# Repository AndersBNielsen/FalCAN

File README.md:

# FalCAN Probe

A compact USB 2.0 to CAN/RS‑485/RS‑422 hardware probe for interfacing and debugging CAN networks and differential serial buses. Designed in KiCad 9.
Firmware is here: <https://github.com/AndersBNielsen/FalCAN_fw>

## Can I buy one?
You can buy a FalCAN here: https://www.imania.dk/index.php?cPath=204&sort=5a&language=en

## Video overview
https://youtu.be/pHMQbOrLfP4

## Blog post
https://abnielsen.com/falcan

## Overview
- MCU: STM32F042C6Tx (USB FS device)
- CAN transceiver: SN65HVD230
- RS‑485/RS‑422 transceivers: SP3485EN (2x)
- USB‑C receptacle (HCTL HC‑TYPE‑C‑16P‑01A)
- 3.3V LDO regulator: MIC5504‑3.3
- Crystals: 8 MHz and 32.768 kHz
- CAN DE‑9 (female) connector for classic CAN pinout
- Jumpers/headers for boot, CAN, RS‑422/485 routing

Project metadata
- Title: FalCAN Probe
- Company: ABNielsen.com
- Revision: 0
- Board: 4‑layer FR4, ~1.6 mm 

## Repository Structure
- `USB-FalCAN.kicad_sch` — KiCad schematic
- `USB-FalCAN.kicad_pcb` — KiCad PCB layout
- `USB-FalCAN.kicad_pro` — KiCad project file
- `USB-FalCAN.kicad_prl` — KiCad project local settings
- `DSUB-9_... .kicad_mod` — Custom footprint for DE‑9 female connector
- `production/` — Fabrication outputs
  - `bom.csv` — Bill of Materials (includes LCSC part numbers)
  - `designators.csv` — Designator map
  - `positions.csv` — Pick‑and‑place (component positions)
  - `netlist.ipc` — IPC‑D‑356 netlist
  - `backups/` — Historical fabrication snapshots
- `fabrication-toolkit-options.json` — Fabrication/export options

## Key BOM Highlights
From `production/bom.csv`:
- MCU: STM32F042C6Tx (LQFP‑48)
- CAN: SN65HVD230 (SOIC‑8)
- RS‑485/422: SP3485EN (SOIC‑8, 2x)
- USB‑C receptacle: HC‑TYPE‑C‑16P‑01A
- LDO: MIC5504‑3.3
- Crystals: 8 MHz (3225), 32.768 kHz (3215)
- LEDs: Green (D1), Red (D2)
- DE‑9 CAN connector and various pin headers/jumpers

## Fabrication
- KiCad: generator version 9.0; board setup targets a 4‑layer FR4 stackup.
- Use KiCad’s Plot tool to generate Gerbers and drill files (settings are stored in the project). The IPC netlist in `production/netlist.ipc` can be provided to your manufacturer for electrical test.
- Pick‑and‑place: `production/positions.csv`.
- BOM: `production/bom.csv` contains LCSC part numbers to streamline sourcing; DNPs are excluded per `fabrication-toolkit-options.json`.

## Assembly & Bring‑Up
- Power from USB‑C (`VBUS`) with on‑board 3.3 V regulation.
- Boot/Programming: STM32F042 can be programmed via USB DFU or SWD (boot header present). Firmware will be released separately.
- CAN I/O: DE‑9 (male) with `CAN_H` and `CAN_L`; USB‑C provides data connection to host.
- RS‑485/RS‑422: Routing and driver enable/receive enable pins exposed via headers/jumpers.

If JP4 is closed at reset, USB is CDC USART1 for RS422/485.
If JP4 in open, USB is GS_USB CAN

Jumpers can be moved into any position after reset. 

RS-422: Default
Full duplex RS-422: Short JP3 & JP4

RS422/485 can be used in CAN mode using external USB-to-UART via USART1 pins (PB7 is RX and PB6 is TX)

## Status
Hardware files are provided; software/firmware will be licensed and released later.

## License
Hardware design files in this repository are licensed under the Creative Commons Attribution‑ShareAlike 4.0 International (CC BY‑SA 4.0). See `LICENSE-Hardware.md` for the full text.

Software/firmware (when added) will use a separate license.

## Credits
- Author/Company: ABNielsen.com
- EDA: KiCad 9

## Getting a PCB
This project is kindly sponsored by JLCPCB. They offer cheap, professional looking PCBs and super fast delivery.

Step 1: Get the gerber file zip package from the /hardware folder

Step 2: Upload to JLCPCB [https://jlcpcb.com/?from=Anders_N](https://jlcpcb.com/?from=Anders_N)

Step 3: Pick your color, surface finish and order.

You can use these affiliate links to get a board for $2 and also get $123 worth of New User Coupons at: https://jlcpcb.com/?from=Anders_N

And in case you also want to order a 3D-printed case you can use this link. 
How to Get a $7 3D Printing Coupon: [https://3d.jlcpcb.com/?from=Anders3DP](https://jlc3dp.com/?from=Anders_N)

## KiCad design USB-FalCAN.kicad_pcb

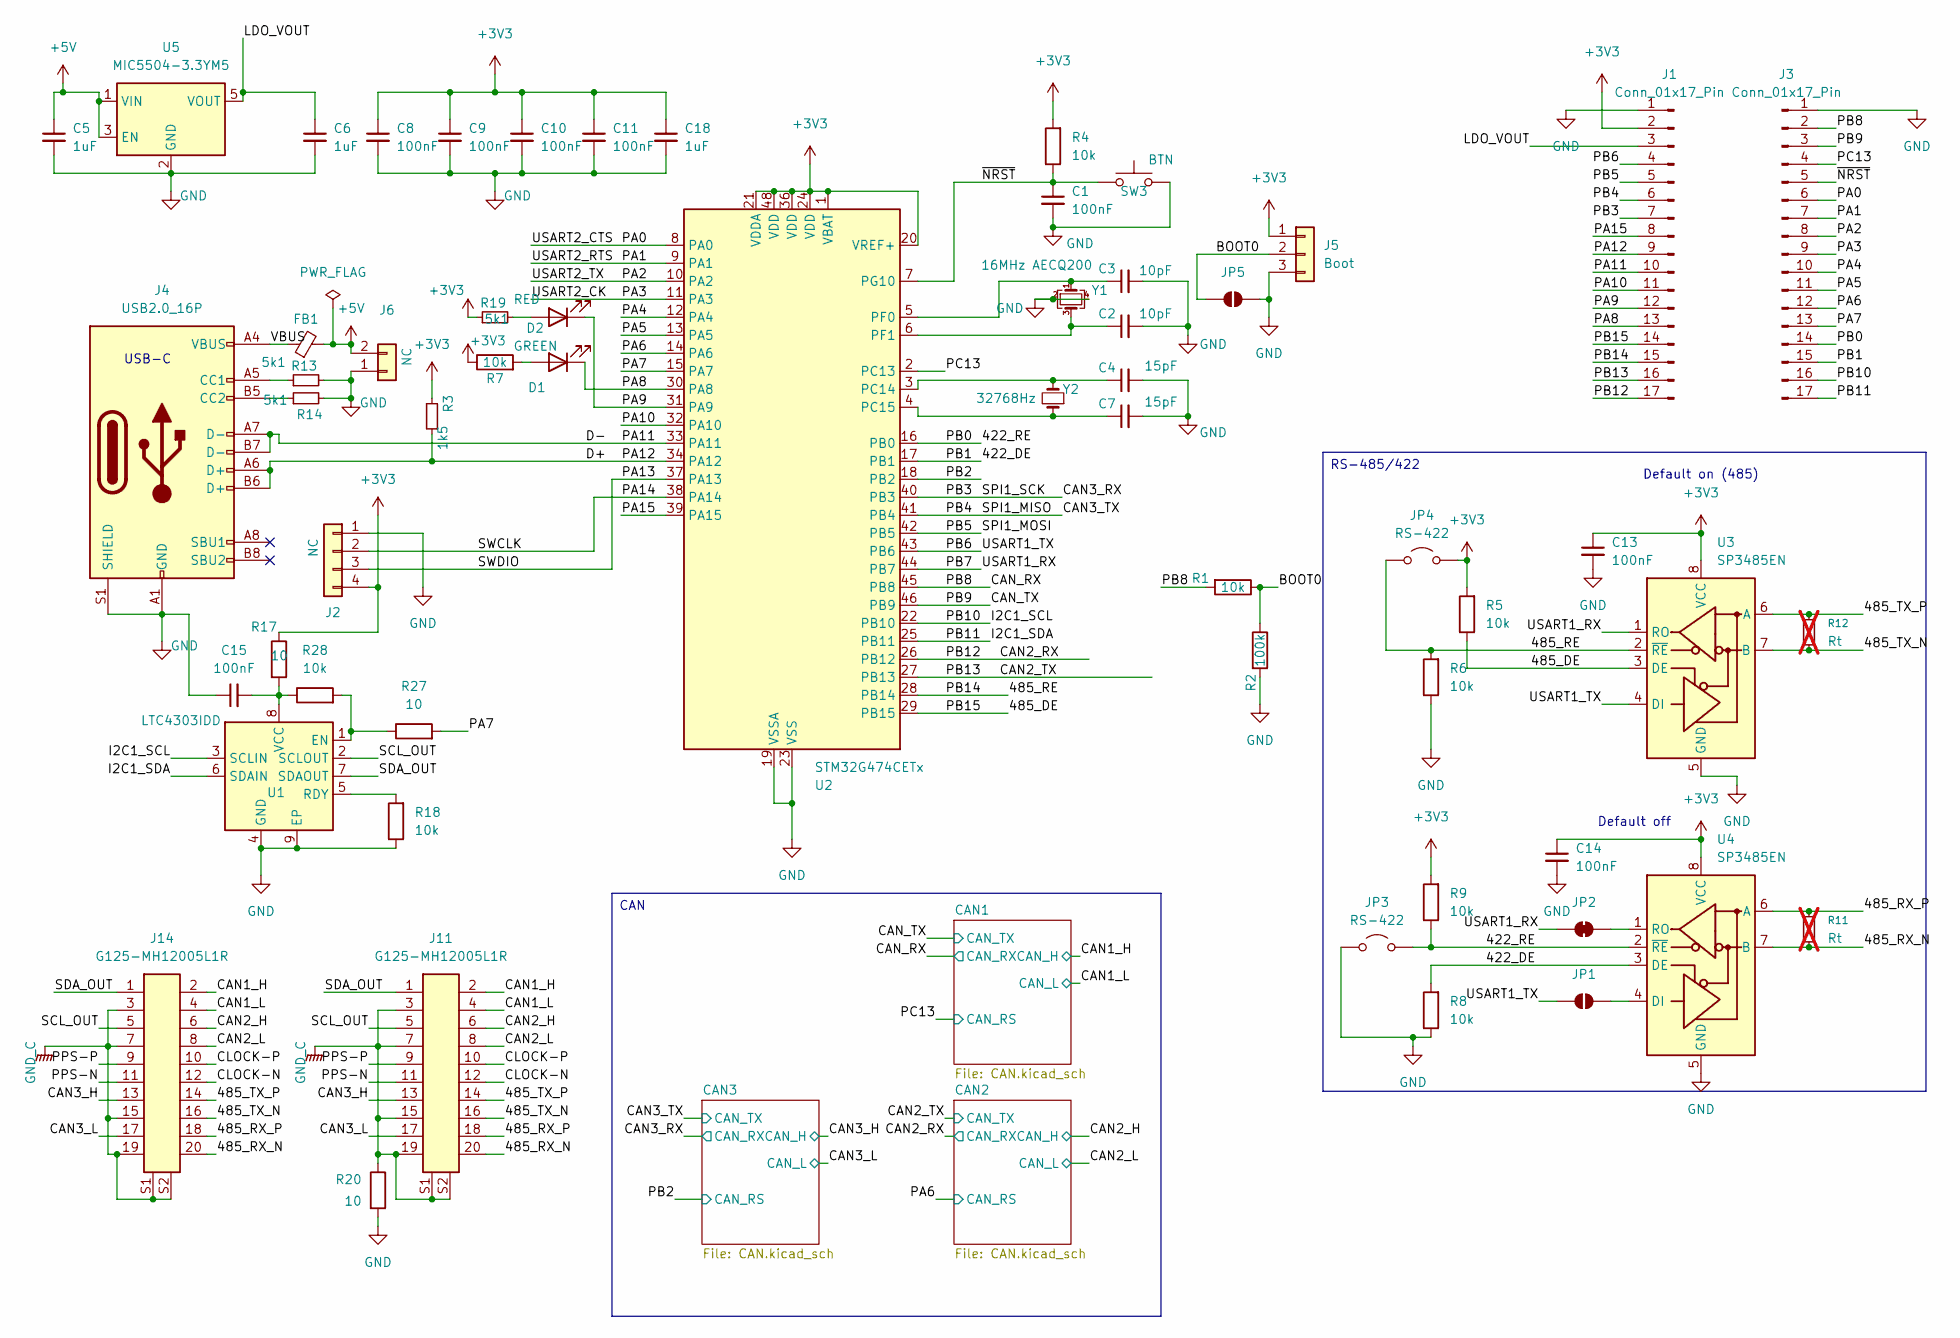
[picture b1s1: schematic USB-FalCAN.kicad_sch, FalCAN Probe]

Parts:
C1, C8, C9, C10, C11, C13, C14, C15: 100nF; C_0402_1005Metric; LCSC C307331
C2, C3: 10pF; C_0402_1005Metric; LCSC C1548
C4, C7: 15pF; C_0402_1005Metric; LCSC C1548
C5, C6, C18: 1uF; C_0805_2012Metric; LCSC C28323
D1: GREEN; LED_0805_2012Metric; LCSC C2297
D2: RED; LED_0805_2012Metric; LCSC C84256
FB1: FerriteBead_Small; L_0603_1608Metric; LCSC C14709
J1, J3: Conn_01x17_Pin; PinHeader_1x17_P2.54mm_Vertical
J2: NC; PinHeader_1x04_P2.54mm_Vertical
J4: USB2.0_16P; USB_C_Receptacle_HCTL_HC-TYPE-C-16P-01A; LCSC C2894897
J5: Boot; PinHeader_1x03_P2.54mm_Vertical
J6: NC; PinHeader_1x02_P2.54mm_Vertical
J11, J14: G125-MH12005L1R; Harwin_G125-MH12005L1R_2x10_P1.25mm_Horizontal; MPN G125-MH12005L1R; LCSC C17484500
JP1, JP5: SolderJumper_2_Open; SolderJumper-2_P1.3mm_Open_RoundedPad1.0x1.5mm
JP2: SolderJumper_2_Bridged; SolderJumper-2_P1.3mm_Bridged_RoundedPad1.0x1.5mm
JP3, JP4: RS-422; PinHeader_1x02_P2.54mm_Vertical
R1, R4, R5, R6, R7, R8, R9, R18, R28: 10k; R_0402_1005Metric; LCSC C25744
R2: 100k; R_0402_1005Metric; LCSC C25744
R3: 1k5; R_0402_1005Metric; LCSC C25867
R11, R12: Rt; R_0805_2012Metric; not fitted
R13, R14, R19: 5k1; R_0402_1005Metric; LCSC C25905
R17, R20, R27: 10; R_0402_1005Metric; LCSC C25744
SW3: BTN; SW_SPST_TL3342; LCSC C318884
U1: LTC4303IDD; DFN-8-1EP_3x3mm_P0.5mm_EP1.66x2.38mm; MPN LTC4303IDD
U2: STM32G474CETx; LQFP-48_7x7mm_P0.5mm
U3, U4: SP3485EN; SOIC-8_3.9x4.9mm_P1.27mm; LCSC C8963
U5: MIC5504-3.3YM5; SOT-23-5; LCSC C3021093
Y1: 16MHz AECQ200; Crystal_SMD_3225-4Pin_3.2x2.5mm; LCSC C5308002
Y2: 32768Hz; Crystal_SMD_3215-2Pin_3.2x1.5mm; LCSC C32346

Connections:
+3V3: C8.1, C9.1, C10.1, C11.1, C13.1, C14.1, C18.1, J1.2, J2.4, J5.1, JP4.2 (B), R3.2, R4.2, R5.2, R7.1, R9.2, R17.1, R19.1, U2.1 (VBAT), U2.20 (VREF+), U2.21 (VDDA), U2.24 (VDD), U2.36 (VDD), U2.48 (VDD), U3.8 (VCC), U4.8 (VCC); also elsewhere on the board
+5V: C5.1, FB1.2, J6.2, U5.1 (VIN), U5.3 (EN)
/422_DE: J3.15, R8.2, U2.17 (PB1), U4.3 (DE)
/422_RE: J3.14, JP3.2 (B), R9.1, U2.16 (PB0), U4.2 (~RE)
/485_DE: J1.14, R5.1, U2.29 (PB15), U3.3 (DE)
/485_RE: J1.15, JP4.1 (A), R6.2, U2.28 (PB14), U3.2 (~RE)
/485_RX_N: J11.20, J14.20, R11.2, U4.7 (B)
/485_RX_P: J11.18, J14.18, R11.1, U4.6 (A)
/485_TX_N: J11.16, J14.16, R12.2, U3.7 (B)
/485_TX_P: J11.14, J14.14, R12.1, U3.6 (A)
/BOOT0: J5.2, JP5.1 (A), R1.1, R2.1
/CAN1_H: J11.2, J14.2; also elsewhere on the board
/CAN1_L: J11.4, J14.4; also elsewhere on the board
/CAN2_H: J11.6, J14.6; also elsewhere on the board
/CAN2_L: J11.8, J14.8; also elsewhere on the board
/CAN2_RX: J1.17, U2.26 (PB12); also elsewhere on the board
/CAN2_TX: J1.16, U2.27 (PB13); also elsewhere on the board
/CAN3_H: J11.13, J14.13; also elsewhere on the board
/CAN3_L: J11.17, J14.17; also elsewhere on the board
/CAN3_RX: J1.7, U2.40 (PB3); also elsewhere on the board
/CAN3_TX: J1.6, U2.41 (PB4); also elsewhere on the board
/CAN_RX: J3.2, R1.2, U2.45 (PB8); also elsewhere on the board
/CAN_TX: J3.3, U2.46 (PB9); also elsewhere on the board
/CLOCK-N: J11.12, J14.12
/CLOCK-P: J11.10, J14.10
/D+: J1.9, J4.A6 (D+), J4.B6 (D+), R3.1, U2.34 (PA12)
/D-: J1.10, J4.A7 (D-), J4.B7 (D-), U2.33 (PA11)
/I2C1_SCL: J3.16, U1.3 (SCLIN), U2.22 (PB10)
/I2C1_SDA: J3.17, U1.6 (SDAIN), U2.25 (PB11)
/LDO_VOUT: C6.1, J1.3, U5.5 (VOUT)
/PA0: J3.6, U2.8 (PA0)
/PA1: J3.7, U2.9 (PA1)
/PA2: J3.8, U2.10 (PA2)
/PA3: J3.9, U2.11 (PA3)
/PA4: J3.10, U2.12 (PA4)
/PA5: J3.11, U2.13 (PA5)
/PA6: J3.12, U2.14 (PA6); also elsewhere on the board
/PA7: J3.13, R27.2, U2.15 (PA7)
/PA8: D1.1 (K), J1.13, U2.30 (PA8)
/PA9: D2.1 (K), J1.12, U2.31 (PA9)
/PA10: J1.11, U2.32 (PA10)
/PA13: J2.3, U2.37 (PA13)
/PA14: J2.2, U2.38 (PA14)
/PA15: J1.8, U2.39 (PA15)
/PB2: U2.18 (PB2); also elsewhere on the board
/PB5: J1.5, U2.42 (PB5)
/PB6: J1.4, JP1.1 (A), U2.43 (PB6), U3.4 (DI)
/PB7: JP2.1 (A), U2.44 (PB7), U3.1 (RO)
/PC13: J3.4, U2.2 (PC13); also elsewhere on the board
/PPS-N: J11.11, J14.11
/PPS-P: J11.9, J14.9
/SCL_OUT: J11.5, J14.5, U1.2 (SCLOUT)
/SDA_OUT: J11.1, J14.1, U1.7 (SDAOUT)
/VBUS: FB1.1, J4.A4 (VBUS), J4.A9 (VBUS), J4.B4 (VBUS), J4.B9 (VBUS)
/~NRST: C1.1, J3.5, R4.1, SW3.1, U2.7 (PG10)
GND: C1.2, C2.2, C3.2, C4.2, C5.2, C6.2, C7.2, C8.2, C9.2, C10.2, C11.2, C13.2, C14.2, C15.1, C18.2, J1.1, J2.1, J3.1, J4.A1 (GND), J4.A12 (GND), J4.B1 (GND), J4.B12 (GND), J4.S1 (SHIELD), J5.3, J6.1, JP3.1 (A), JP5.2 (B), R2.2, R6.1, R8.1, R13.2, R14.2, R18.1, R20.2, SW3.2, U1.4 (GND), U1.9 (EP), U2.19 (VSSA), U2.23 (VSS), U2.35 (VSS), U2.47 (VSS), U3.5 (GND), U4.5 (GND), U5.2 (GND), Y1.2, Y1.4; also elsewhere on the board
GND_C: J11.3, J11.7, J11.15, J11.19, J11.S1 (MP), J11.S2 (MP), J14.3, J14.7, J14.15, J14.19, J14.S1 (MP), J14.S2 (MP), R20.1
unnamed: D1.2 (A), R7.2
unnamed: D2.2 (A), R19.2
unnamed: J4.A5 (CC1), R13.1
unnamed: J4.B5 (CC2), R14.1
unnamed: JP1.2 (B), U4.4 (DI)
unnamed: JP2.2 (B), U4.1 (RO)
unnamed: R27.1, R28.2, U1.1 (EN)
unnamed: R18.2, U1.5 (RDY)
unnamed: C15.2, R17.2, R28.1, U1.8 (VCC)
unnamed: C4.1, U2.3 (PC14), Y2.2
unnamed: C7.1, U2.4 (PC15), Y2.1
unnamed: C3.1, U2.5 (PF0), Y1.1
unnamed: C2.1, U2.6 (PF1), Y1.3

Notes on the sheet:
Default off
USB-C
Default on (485)
RS-485/422
CAN

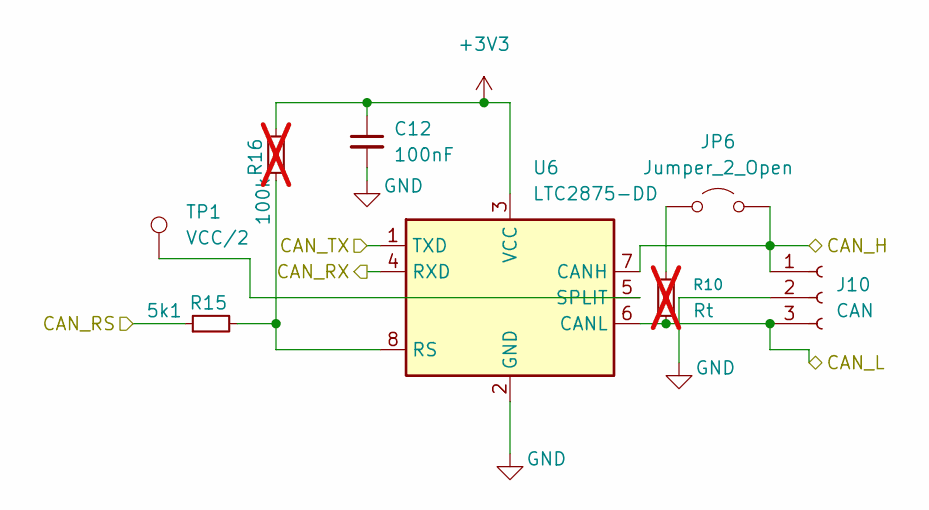
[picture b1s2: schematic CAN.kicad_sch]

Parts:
C12: 100nF; C_0402_1005Metric; LCSC C307331
J10: CAN; PinHeader_1x03_P2.54mm_Vertical
JP6: Jumper_2_Open; PinHeader_1x02_P2.54mm_Vertical
R10: Rt; R_0805_2012Metric; not fitted
R15: 5k1; R_0402_1005Metric; LCSC C25905
R16: 100k; R_0402_1005Metric; LCSC C25905; not fitted
TP1: VCC/2; TestPoint_Pad_D1.0mm
U6: LTC2875-DD; DFN-8-1EP_3x3mm_P0.5mm_EP1.66x2.38mm; LCSC C683035

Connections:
+3V3: C12.1, R16.2, U6.3 (VCC); also elsewhere on the board
/CAN1_H: J10.1, JP6.2 (B), U6.7 (CANH); also elsewhere on the board
/CAN1_L: J10.3, R10.2, U6.6 (CANL); also elsewhere on the board
/CAN_RX: U6.4 (RXD); also elsewhere on the board
/CAN_TX: U6.1 (TXD); also elsewhere on the board
/PC13: R15.1; also elsewhere on the board
GND: C12.2, J10.2, U6.2 (GND), U6.9 (GND); also elsewhere on the board
unnamed: JP6.1 (A), R10.1
unnamed: R15.2, R16.1, U6.8 (RS)
unnamed: TP1.1 (1_1), U6.5 (SPLIT)

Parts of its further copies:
C16, C17: 100nF; C_0402_1005Metric; LCSC C307331
J12, J13: CAN; PinHeader_1x03_P2.54mm_Vertical
JP7, JP8: Jumper_2_Open; PinHeader_1x02_P2.54mm_Vertical
R21, R24: 5k1; R_0402_1005Metric; LCSC C25905
R22, R25: 100k; R_0402_1005Metric; LCSC C25905; not fitted
R23, R26: Rt; R_0805_2012Metric; not fitted
TP2, TP3: VCC/2; TestPoint_Pad_D1.0mm
U7, U8: LTC2875-DD; DFN-8-1EP_3x3mm_P0.5mm_EP1.66x2.38mm; LCSC C683035

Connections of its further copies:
+3V3: C16.1, C17.1, R22.2, R25.2, U7.3 (VCC), U8.3 (VCC); also elsewhere on the board
/CAN2_H: J12.1, JP7.2 (B), U7.7 (CANH); also elsewhere on the board
/CAN2_L: J12.3, R23.2, U7.6 (CANL); also elsewhere on the board
/CAN2_RX: U7.4 (RXD); also elsewhere on the board
/CAN2_TX: U7.1 (TXD); also elsewhere on the board
/CAN3_H: J13.1, JP8.2 (B), U8.7 (CANH); also elsewhere on the board
/CAN3_L: J13.3, R26.2, U8.6 (CANL); also elsewhere on the board
/CAN3_RX: U8.4 (RXD); also elsewhere on the board
/CAN3_TX: U8.1 (TXD); also elsewhere on the board
/PA6: R21.1; also elsewhere on the board
/PB2: R24.1; also elsewhere on the board
GND: C16.2, C17.2, J12.2, J13.2, U7.2 (GND), U7.9 (GND), U8.2 (GND), U8.9 (GND); also elsewhere on the board
unnamed: JP7.1 (A), R23.1
unnamed: JP8.1 (A), R26.1
unnamed: R21.2, R22.1, U7.8 (RS)
unnamed: TP2.1 (1_1), U7.5 (SPLIT)
unnamed: R24.2, R25.1, U8.8 (RS)
unnamed: TP3.1 (1_1), U8.5 (SPLIT)

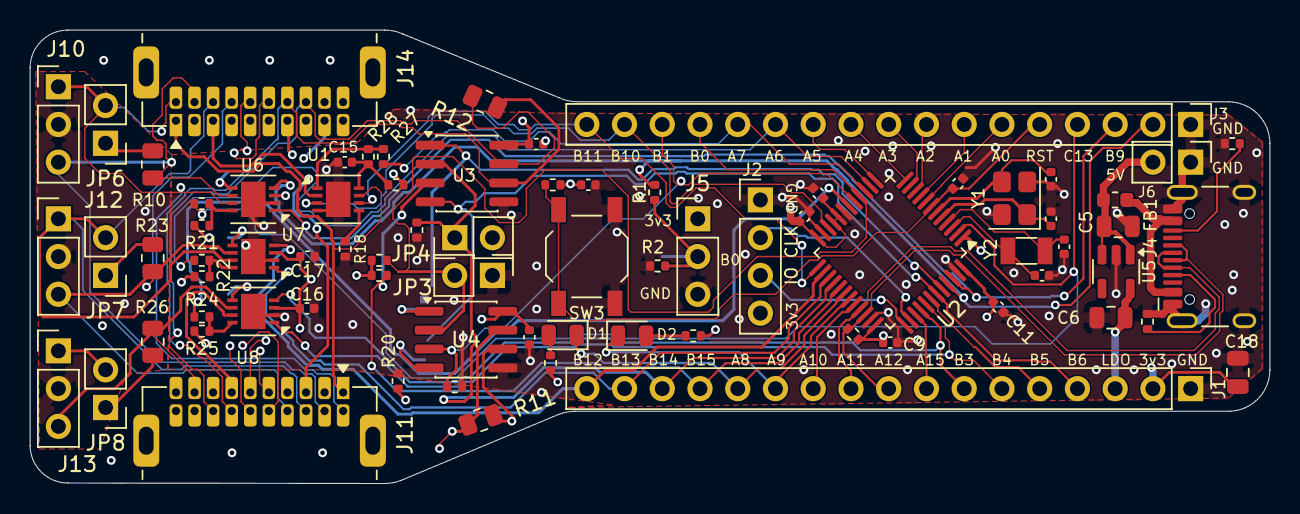
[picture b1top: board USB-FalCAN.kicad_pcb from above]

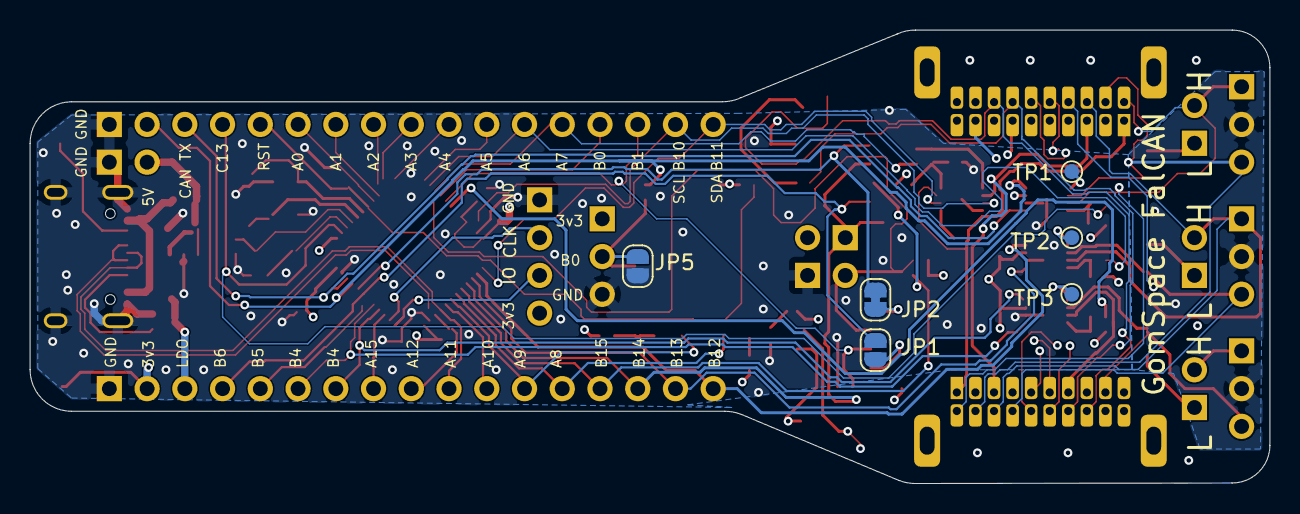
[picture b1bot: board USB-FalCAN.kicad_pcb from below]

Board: 6 copper layers, 83.4 x 30.5 mm, 82 parts (6 on the bottom side), 79 nets.

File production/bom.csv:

Designator,Footprint,Quantity,Value,LCSC Part #
"C1, C10, C11, C12, C13, C14, C15, C16, C17, C8, C9",0402,11,100nF,C307331
C18,0805,1,1uF,
"C2, C3",0402,2,10pF,C1548
"C4, C7",0402,2,15pF,C1548
"C5, C6",0805,2,1uF,C28323
D1,0805,1,GREEN,C2297
D2,0805,1,RED,C84256
FB1,0603,1,FerriteBead_Small,C14709
"J1, J3",PinHeader_1x17_P2.54mm_Vertical,2,Conn_01x17_Pin,
"J10, J12, J13",PinHeader_1x03_P2.54mm_Vertical,3,CAN,
"J11, J14",Harwin_G125-MH12005L1R_2x10_P1.25mm_Horizontal,2,G125-MH12005L1R,C17484500
J2,PinHeader_1x04_P2.54mm_Vertical,1,NC,
J4,USB_C_Receptacle_HCTL_HC-TYPE-C-16P-01A,1,USB2.0_16P,C2894897
J5,PinHeader_1x03_P2.54mm_Vertical,1,Boot,
J6,PinHeader_1x02_P2.54mm_Vertical,1,NC,
"JP3, JP4",PinHeader_1x02_P2.54mm_Vertical,2,RS-422,
"JP6, JP7, JP8",PinHeader_1x02_P2.54mm_Vertical,3,Jumper_2_Open,
"R1, R18, R28, R4, R5, R6, R7, R8, R9",0402,9,10k,C25744
"R13, R14, R15, R19, R21, R24",0402,6,5k1,C25905 
"R17, R20, R27",0402,3,10,C25744
R2,0402,1,100k,
R3,0402,1,1k5,C25867
SW3,SW_SPST_TL3342,1,BTN,C318884
"TP1, TP2, TP3",TestPoint_Pad_D1.0mm,3,VCC/2,
U1,DFN-8-1EP_3x3mm_P0.5mm_EP1.66x2.38mm,1,LTC4303IDD,LTC4303IDD
U2,LQFP-48_7x7mm_P0.5mm,1,STM32G474CETx,
"U3, U4",SOIC-8_3.9x4.9mm_P1.27mm,2,SP3485EN,C8963
U5,SOT-23-5,1,MIC5504-3.3YM5,C3021093
"U6, U7, U8",DFN-8-1EP_3x3mm_P0.5mm_EP1.66x2.38mm,3,LTC2875-DD,C683035
Y1,Crystal_SMD_3225-4Pin_3.2x2.5mm,1,16MHz AECQ200,C5308002
Y2,Crystal_SMD_3215-2Pin_3.2x1.5mm,1,32768Hz,C32346

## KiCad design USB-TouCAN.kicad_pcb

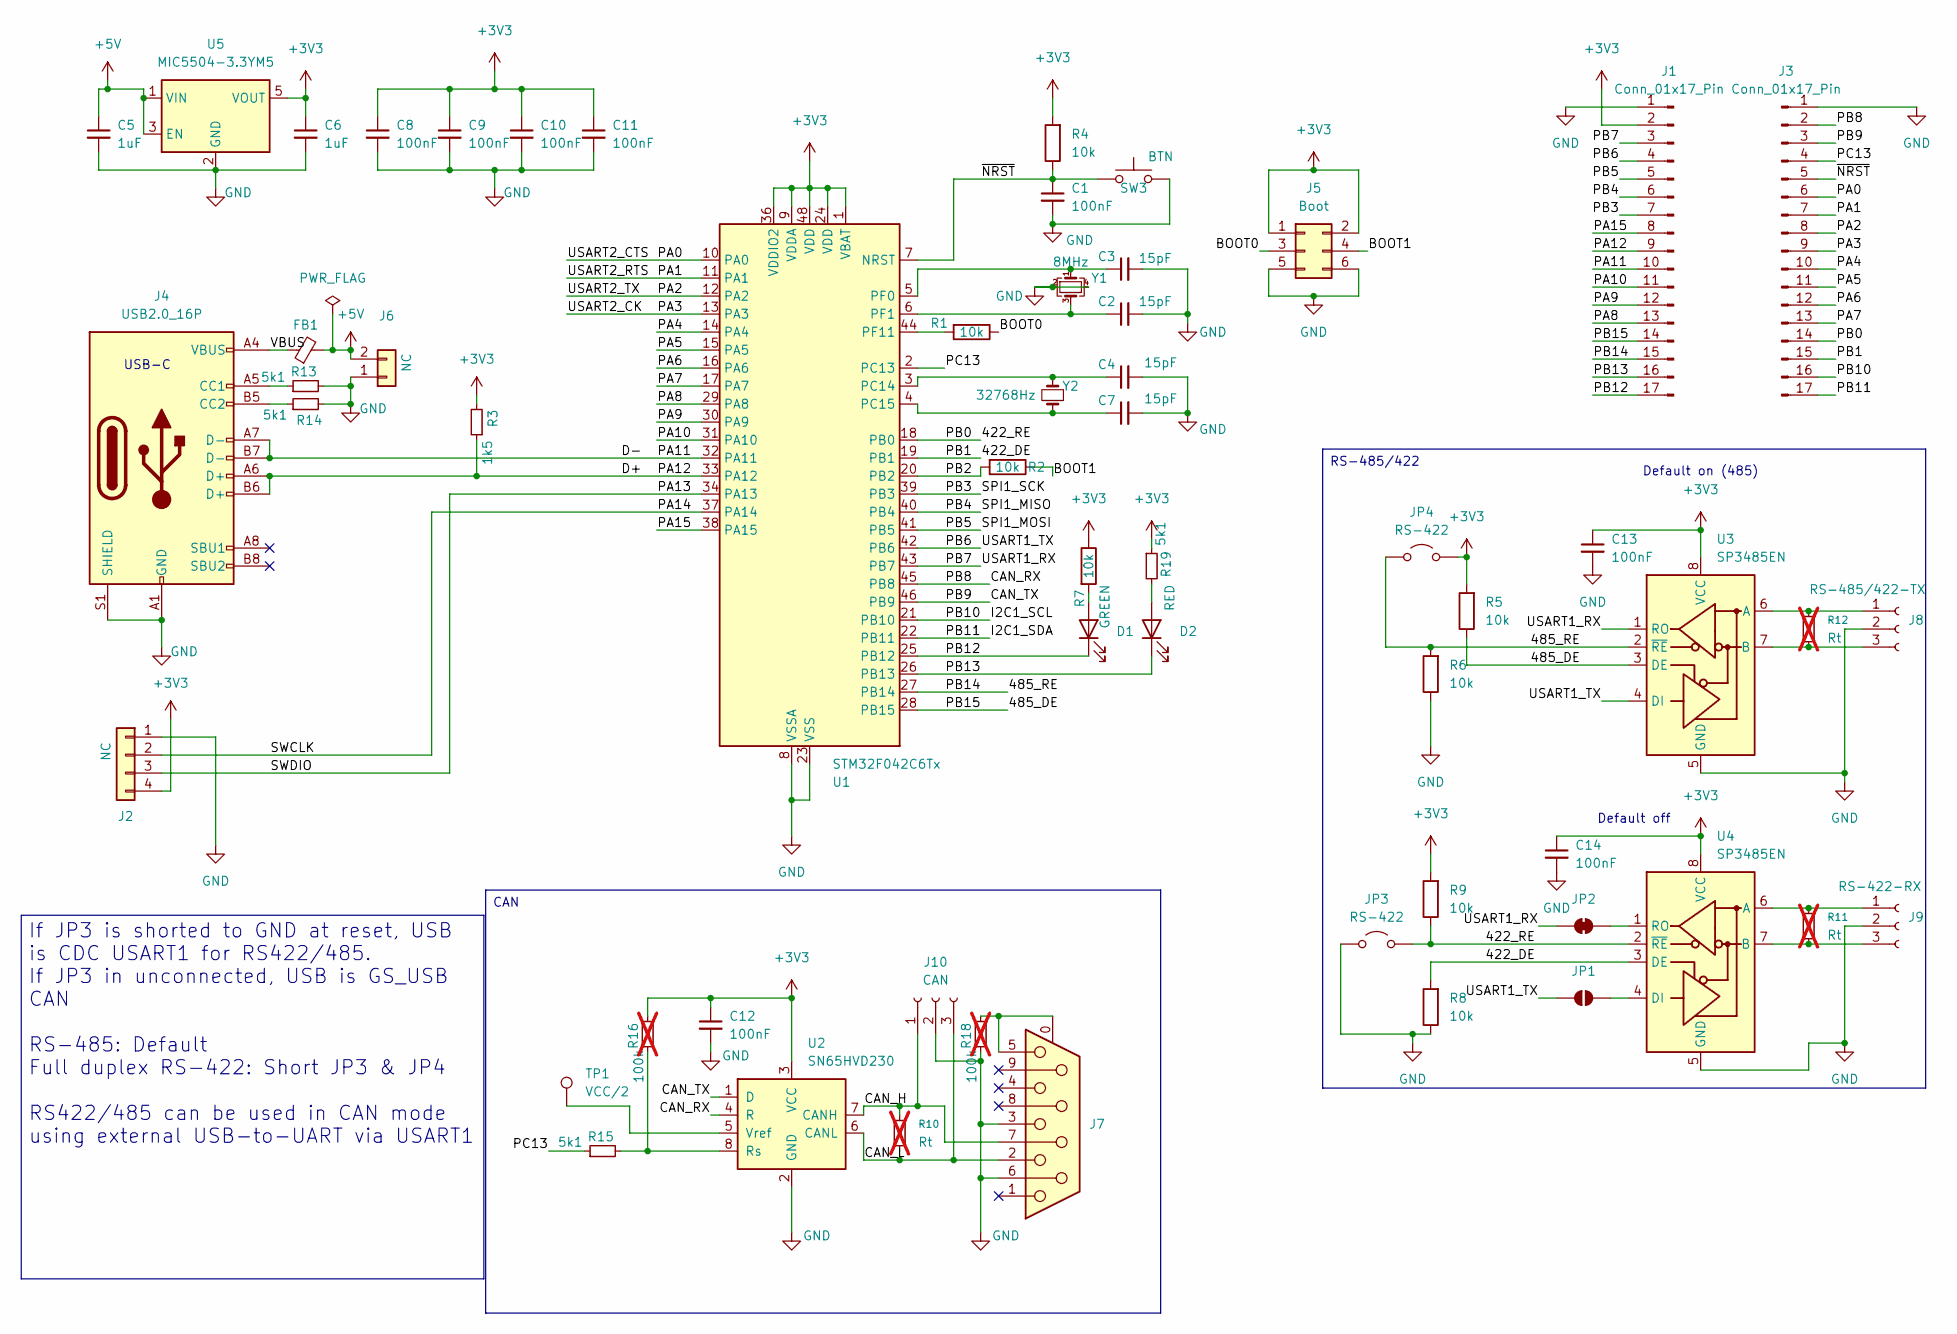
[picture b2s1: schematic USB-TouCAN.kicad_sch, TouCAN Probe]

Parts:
C1, C8, C9, C10, C11, C12, C13, C14: 100nF; C_0402_1005Metric; LCSC C307331
C2, C3, C4, C7: 15pF; C_0402_1005Metric; LCSC C1548
C5, C6: 1uF; C_0805_2012Metric; LCSC C28323
D1: GREEN; LED_0805_2012Metric; LCSC C2297
D2: RED; LED_0805_2012Metric; LCSC C84256
FB1: FerriteBead_Small; L_0603_1608Metric; LCSC C14709
J1, J3: Conn_01x17_Pin; PinHeader_1x17_P2.54mm_Vertical
J2: NC; PinHeader_1x04_P2.54mm_Vertical
J4: USB2.0_16P; USB_C_Receptacle_HCTL_HC-TYPE-C-16P-01A; LCSC C2894897
J5: Boot; PinHeader_2x03_P2.54mm_Vertical
J6: NC; PinHeader_1x02_P2.54mm_Vertical
J7: DE9_Receptacle; DSUB-9_Female_Horizontal_P2.77x2.84mm_EdgePinOffset7.70mm_H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; LCSC C19077344
J8: RS-485/422-TX; PinHeader_1x03_P2.54mm_Vertical
J9: RS-422-RX; PinHeader_1x03_P2.54mm_Vertical
J10: CAN; PinHeader_1x03_P2.54mm_Vertical
JP1: SolderJumper_2_Open; SolderJumper-2_P1.3mm_Open_RoundedPad1.0x1.5mm
JP2: SolderJumper_2_Bridged; SolderJumper-2_P1.3mm_Bridged_RoundedPad1.0x1.5mm
JP3, JP4: RS-422; PinHeader_1x02_P2.54mm_Vertical
R1, R2, R4, R5, R6, R7, R8, R9: 10k; R_0402_1005Metric; LCSC C25744
R3: 1k5; R_0402_1005Metric; LCSC C25867
R10, R11, R12: Rt; R_0805_2012Metric; not fitted
R13, R14, R15, R19: 5k1; R_0402_1005Metric; LCSC C25905
R16, R18: 100k; R_0402_1005Metric; LCSC C25905; not fitted
SW3: BTN; SW_SPST_TL3342; LCSC C318884
TP1: VCC/2; TestPoint_Pad_D1.0mm
U1: STM32F042C6Tx; LQFP-48_7x7mm_P0.5mm; LCSC C88447
U2: SN65HVD230; SOIC-8_3.9x4.9mm_P1.27mm; LCSC C12084
U3, U4: SP3485EN; SOIC-8_3.9x4.9mm_P1.27mm; LCSC C8963
U5: MIC5504-3.3YM5; SOT-23-5; LCSC C3021093
Y1: 8MHz; Crystal_SMD_3225-4Pin_3.2x2.5mm; LCSC C5308002
Y2: 32768Hz; Crystal_SMD_3215-2Pin_3.2x1.5mm; LCSC C32346

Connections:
+3V3: C6.1, C8.1, C9.1, C10.1, C11.1, C12.1, C13.1, C14.1, J1.2, J2.4, J5.1, J5.2, JP4.2 (B), R3.2, R4.2, R5.2, R7.1, R9.2, R16.2, R19.1, U1.1 (VBAT), U1.9 (VDDA), U1.24 (VDD), U1.36 (VDDIO2), U1.48 (VDD), U2.3 (VCC), U3.8 (VCC), U4.8 (VCC), U5.5 (VOUT)
+5V: C5.1, FB1.2, J6.2, U5.1 (VIN), U5.3 (EN)
/422_DE: J3.15, R8.2, U1.19 (PB1), U4.3 (DE)
/422_RE: J3.14, JP3.2 (B), R9.1, U1.18 (PB0), U4.2 (~RE)
/485_DE: J1.14, R5.1, U1.28 (PB15), U3.3 (DE)
/485_RE: J1.15, JP4.1 (A), R6.2, U1.27 (PB14), U3.2 (~RE)
/BOOT0: J5.3, R1.1
/BOOT1: J5.4, R2.1
/CAN_H: J7.7, J10.1, R10.1, U2.7 (CANH)
/CAN_L: J7.2, J10.3, R10.2, U2.6 (CANL)
/CAN_RX: J3.2, U1.45 (PB8), U2.4 (R)
/CAN_TX: J3.3, U1.46 (PB9), U2.1 (D)
/D+: J1.9, J4.A6 (D+), J4.B6 (D+), R3.1, U1.33 (PA12)
/D-: J1.10, J4.A7 (D-), J4.B7 (D-), U1.32 (PA11)
/I2C1_SCL: J3.16, U1.21 (PB10)
/I2C1_SDA: J3.17, U1.22 (PB11)
/PA0: J3.6, U1.10 (PA0)
/PA1: J3.7, U1.11 (PA1)
/PA2: J3.8, U1.12 (PA2)
/PA3: J3.9, U1.13 (PA3)
/PA4: J3.10, U1.14 (PA4)
/PA5: J3.11, U1.15 (PA5)
/PA6: J3.12, U1.16 (PA6)
/PA7: J3.13, U1.17 (PA7)
/PA8: J1.13, U1.29 (PA8)
/PA9: J1.12, U1.30 (PA9)
/PA10: J1.11, U1.31 (PA10)
/PA13: J2.3, U1.34 (PA13)
/PA14: J2.2, U1.37 (PA14)
/PA15: J1.8, U1.38 (PA15)
/PB2: R2.2, U1.20 (PB2)
/PB3: J1.7, U1.39 (PB3)
/PB4: J1.6, U1.40 (PB4)
/PB5: J1.5, U1.41 (PB5)
/PB6: J1.4, JP1.1 (A), U1.42 (PB6), U3.4 (DI)
/PB7: J1.3, JP2.1 (A), U1.43 (PB7), U3.1 (RO)
/PB12: D1.1 (K), J1.17, U1.25 (PB12)
/PB13: D2.1 (K), J1.16, U1.26 (PB13)
/PC13: J3.4, R15.1, U1.2 (PC13)
/VBUS: FB1.1, J4.A4 (VBUS), J4.A9 (VBUS), J4.B4 (VBUS), J4.B9 (VBUS)
/~NRST: C1.1, J3.5, R4.1, SW3.1, U1.7 (NRST)
GND: C1.2, C2.2, C3.2, C4.2, C5.2, C6.2, C7.2, C8.2, C9.2, C10.2, C11.2, C12.2, C13.2, C14.2, J1.1, J2.1, J3.1, J4.A1 (GND), J4.A12 (GND), J4.B1 (GND), J4.B12 (GND), J4.S1 (SHIELD), J5.5, J5.6, J6.1, J7.3, J7.6, J8.2, J9.2, J10.2, JP3.1 (A), R6.1, R8.1, R13.2, R14.2, R18.1, SW3.2, U1.8 (VSSA), U1.23 (VSS), U1.35 (VSS), U1.47 (VSS), U2.2 (GND), U3.5 (GND), U4.5 (GND), U5.2 (GND), Y1.2, Y1.4
unnamed: D1.2 (A), R7.2
unnamed: D2.2 (A), R19.2
unnamed: J4.A5 (CC1), R13.1
unnamed: J4.B5 (CC2), R14.1
unnamed: J7.0 (PAD), J7.5, R18.2
unnamed: J8.1, R12.1, U3.6 (A)
unnamed: J8.3, R12.2, U3.7 (B)
unnamed: J9.1, R11.1, U4.6 (A)
unnamed: J9.3, R11.2, U4.7 (B)
unnamed: JP1.2 (B), U4.4 (DI)
unnamed: JP2.2 (B), U4.1 (RO)
unnamed: C4.1, U1.3 (PC14), Y2.2
unnamed: C7.1, U1.4 (PC15), Y2.1
unnamed: C3.1, U1.5 (PF0), Y1.1
unnamed: C2.1, U1.6 (PF1), Y1.3
unnamed: R1.2, U1.44 (PF11)
unnamed: R15.2, R16.1, U2.8 (Rs)
unnamed: TP1.1, U2.5 (Vref)

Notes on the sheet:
Default off
USB-C
Default on (485)
RS-485/422
CAN
If JP3 is shorted to GND at reset, USB is CDC USART1 for RS422/485. If JP3 in unconnected, USB is GS_USB CAN RS-485: Default Full duplex RS-422: Short JP3 & JP4 RS422/485 can be used in CAN mode using external USB-to-UART via USART1

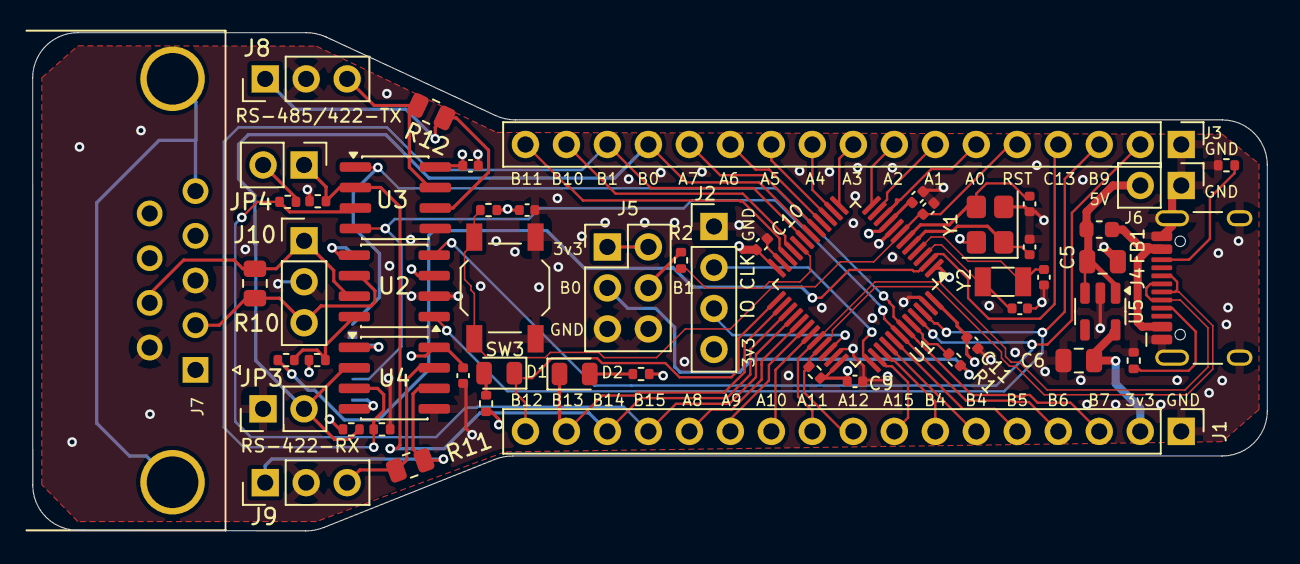
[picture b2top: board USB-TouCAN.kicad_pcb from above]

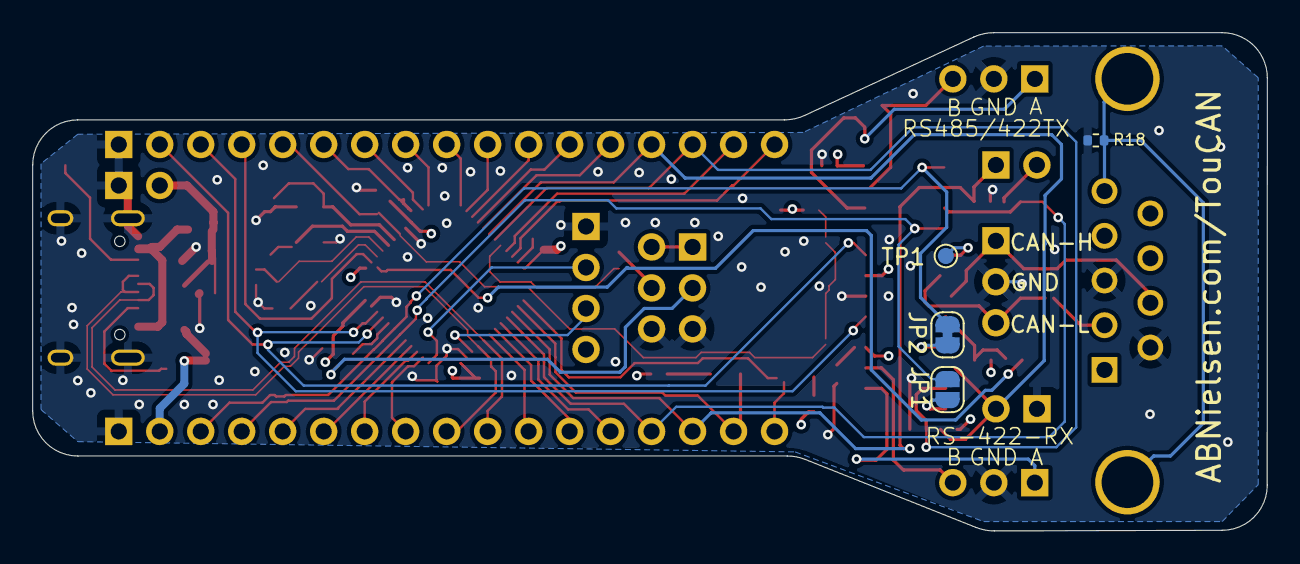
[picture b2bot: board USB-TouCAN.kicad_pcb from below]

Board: 4 copper layers, 76.5 x 30.9 mm, 58 parts (4 on the bottom side), 60 nets.

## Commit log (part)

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2026-02-01 Initial release
2026-02-04 Cleanup after PCB review
2026-02-27 Update schematic help text
2026-04-06 Rename to FalCAN
2026-04-06 Replace USB-TouCAN files with USB-FalCAN
2026-04-09 Improve silk
